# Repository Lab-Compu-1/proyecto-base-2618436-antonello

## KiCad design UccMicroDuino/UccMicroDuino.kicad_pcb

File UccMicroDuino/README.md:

modificacion - Nicolas Antonello 2618436

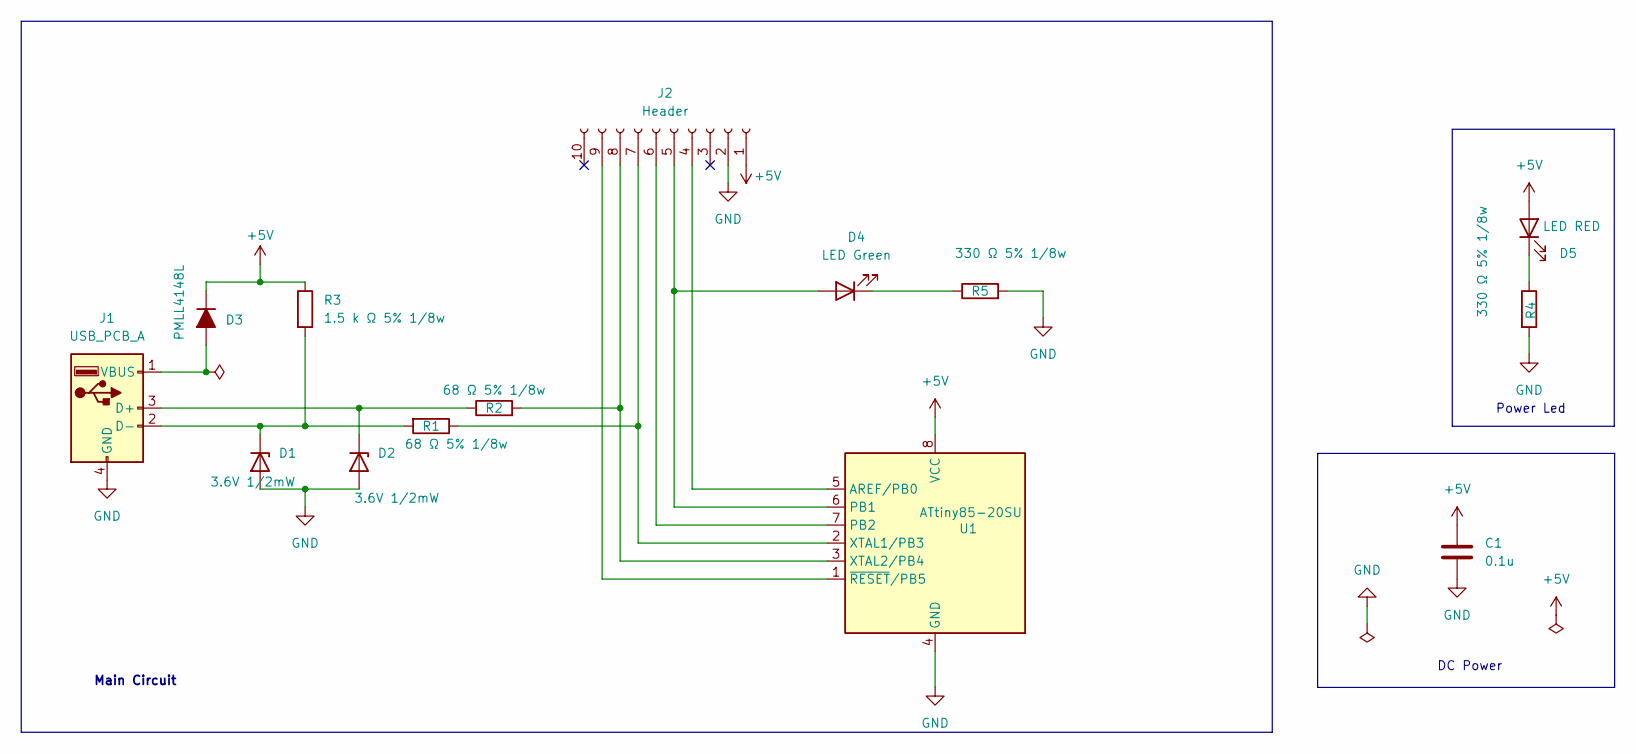
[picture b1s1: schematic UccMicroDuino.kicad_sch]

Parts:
C1: 0.1u; C_0805_2012Metric_Pad1.18x1.45mm_HandSolder
D1, D2: 3.6V 1/2mW; D_SOD-123
D3: PMLL4148L; D_MiniMELF
D4: LED Green; D_SOD-123
D5: LED RED; ledSMD
J1: USB_PCB_A; USB_A_UCC
J2: Header; PinHeader_1x10_P2.54mm_Vertical
R1, R2: 68 Ω 5% 1/8w; R_0805_2012Metric_Pad1.20x1.40mm_HandSolder
R3: 1.5 k Ω 5% 1/8w; R_0805_2012Metric_Pad1.20x1.40mm_HandSolder
R4, R5: 330 Ω 5% 1/8w; R_0805_2012Metric_Pad1.20x1.40mm_HandSolder
U1: ATtiny85-20SU; SOIC-8W_5.3x5.3mm_P1.27mm

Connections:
+5V: C1.1, D3.1 (K), D5.2 (A), J2.1, R3.1, U1.8 (VCC)
GND: C1.2, D1.2 (A), D2.2 (A), J1.4 (GND), J2.2, R4.2, R5.2, U1.4 (GND)
unnamed: D1.1 (K), J1.2 (D-), R1.2, R3.2
unnamed: D2.1 (K), J1.3 (D+), R2.1
unnamed: D3.2 (A), J1.1 (VBUS)
unnamed: D4.2 (A), J2.5, U1.6 (PB1)
unnamed: D4.1 (K), R5.1
unnamed: D5.1 (K), R4.1
unnamed: J2.4, U1.5 (AREF/PB0)
unnamed: J2.6, U1.7 (PB2)
unnamed: J2.7, R1.1, U1.2 (XTAL1/PB3)
unnamed: J2.8, R2.2, U1.3 (XTAL2/PB4)
unnamed: J2.9, U1.1 (~RESET/PB5)

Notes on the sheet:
Main Circuit
DC Power
Power Led

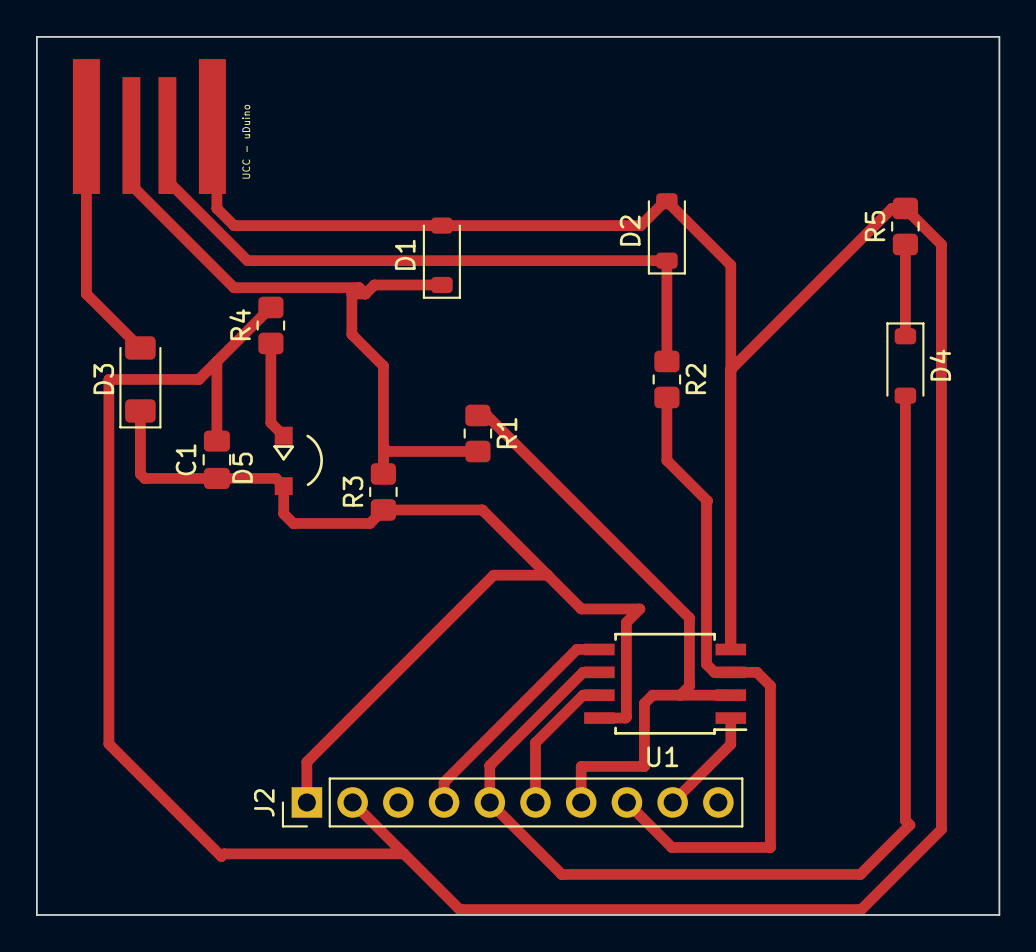
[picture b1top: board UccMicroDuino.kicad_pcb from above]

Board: 2 copper layers, 53.5 x 48.8 mm, 14 parts (0 on the bottom side), 13 nets.

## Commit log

2026-03-30 GitHub Classroom Feedback
2026-03-30 Setting up GitHub Classroom Feedback
2026-06-09 modificacion del proyecto - Nicolas Antonello 2618436
